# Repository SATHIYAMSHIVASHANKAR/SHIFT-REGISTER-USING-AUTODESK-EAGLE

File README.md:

# SHIFT-REGISTER-USING-AUTODESK-EAGLE
DEVELOPING SHIFT REGISTER USING IC 74595 IN AUTODESK EAGLE
***
step 1: In Autodesk Eagle, create a new project under the project sector. Name the file as Shift Register. Now under Shift Register create a Schematic file.
***
step 2: Allocate nessasary grid lines value in the grid section such that the editor page comes with the sutable grid lines
***
step 3: Using Add components tool, take the required parts and place it in the schematic with refernce to the circuit diagram. 
***
step 4: In order to reduce the complexcity in wire connection, introduce bus connection using Bus tool.
***
step 5: In Bus connection, it is mandatory to give Alias name and the Specification. Through this we can connet the Net (wire) conection at ease.
***
step 6: Now connect the components in the schematic using Net tool. 
***
step 7: Refer the data sheet to allocate the values to the components by using Value tool.
***
step 8 Its is mandatory to create a Net class for the ciruit made in Schematic. Create a net class, name it as Power and add the nessasary values to the Member section. Enter the respective terms to Default and Power sections.
***
step 9: To frame the entire circuit, select a Frame of your choice in Add components tool, place it around the circuit in schematic.
***
step 10: Now create a board, such that the diamentions of the board must be 80*60 mm
***
step 11: Move the components into the board and route the components using Air Routeing tool.
***
step 12: Select Polygon tool and extend its strech to the entire board. Name it as Ground. Now by appling Ratsnest tool, the polygon (ground) gets activated.
***
step 13: To give the name to board use Name tool. Enter the appropriate name and place it on the board with the Name Layer activated.
***
step 14: Drill four holes in each corner using Hole tool. By accessing Manufacturing tool we will get to know about the completed PCB board.
***

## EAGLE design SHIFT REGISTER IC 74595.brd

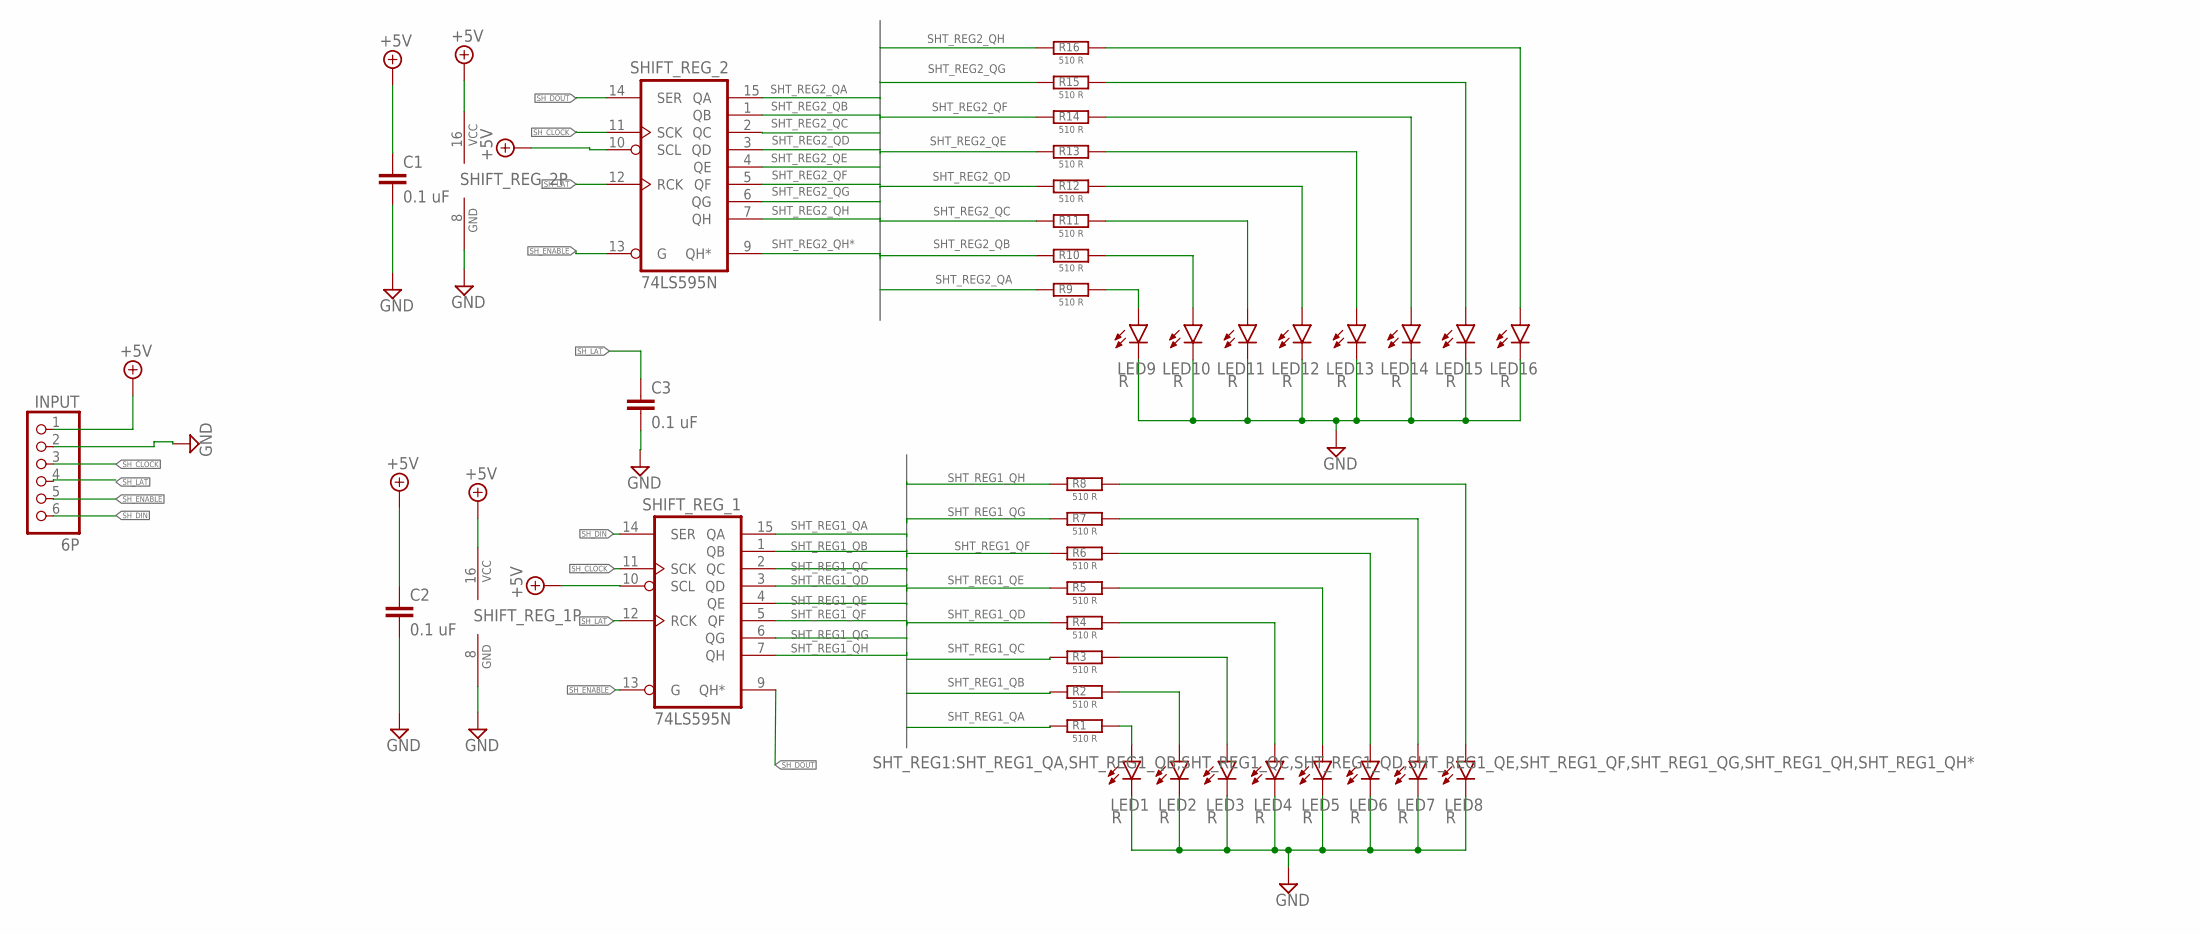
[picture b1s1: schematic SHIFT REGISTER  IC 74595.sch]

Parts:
C1, C2, C3: 0.1 uF; C050-030X075
INPUT: 6P; 1X06/90
LED1, LED2, LED3, LED4, LED5, LED6, LED7, LED8, LED9, LED10, LED11, LED12, LED13, LED14, LED15, LED16: R; LED5MM
R1, R2, R3, R4, R5, R6, R7, R8, R9, R10, R11, R12, R13, R14, R15, R16: 510 R; 0207/10
SHIFT_REG_1, SHIFT_REG_2: 74LS595N; DIL16

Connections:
+5V: C1.1, C2.1, INPUT.1, SHIFT_REG_1.10 (SCL), SHIFT_REG_1.16 (VCC), SHIFT_REG_2.10 (SCL), SHIFT_REG_2.16 (VCC)
GND: C1.2, C2.2, C3.2, INPUT.2, LED1.K (C), LED2.K (C), LED3.K (C), LED4.K (C), LED5.K (C), LED6.K (C), LED7.K (C), LED8.K (C), LED9.K (C), LED10.K (C), LED11.K (C), LED12.K (C), LED13.K (C), LED14.K (C), LED15.K (C), LED16.K (C), SHIFT_REG_1.8 (GND), SHIFT_REG_2.8 (GND)
unnamed: LED1.A, R1.2
unnamed: LED2.A, R2.2
unnamed: LED3.A, R3.2
unnamed: LED4.A, R4.2
unnamed: LED5.A, R5.2
unnamed: LED6.A, R6.2
unnamed: LED7.A, R7.2
unnamed: LED8.A, R8.2
unnamed: LED9.A, R9.2
unnamed: LED10.A, R10.2
unnamed: LED11.A, R11.2
unnamed: LED12.A, R12.2
unnamed: LED13.A, R13.2
unnamed: LED14.A, R14.2
unnamed: LED15.A, R15.2
unnamed: LED16.A, R16.2
SHT_REG1_QA: R1.1, SHIFT_REG_1.15 (QA)
SHT_REG1_QB: R2.1, SHIFT_REG_1.1 (QB)
SHT_REG1_QC: R3.1, SHIFT_REG_1.2 (QC)
SHT_REG1_QD: R4.1, SHIFT_REG_1.3 (QD)
SHT_REG1_QE: R5.1, SHIFT_REG_1.4 (QE)
SHT_REG1_QF: R6.1, SHIFT_REG_1.5 (QF)
SHT_REG1_QG: R7.1, SHIFT_REG_1.6 (QG)
SHT_REG1_QH: R8.1, SHIFT_REG_1.7 (QH)
SHT_REG2_QA: R9.1, SHIFT_REG_2.15 (QA)
SHT_REG2_QB: R10.1, SHIFT_REG_2.1 (QB)
SHT_REG2_QC: R11.1, SHIFT_REG_2.2 (QC)
SHT_REG2_QD: R12.1, SHIFT_REG_2.3 (QD)
SHT_REG2_QE: R13.1, SHIFT_REG_2.4 (QE)
SHT_REG2_QF: R14.1, SHIFT_REG_2.5 (QF)
SHT_REG2_QG: R15.1, SHIFT_REG_2.6 (QG)
SHT_REG2_QH: R16.1, SHIFT_REG_2.7 (QH)
SHT_REG2_QH*: SHIFT_REG_2.9 (QH*)
SH_CLOCK: INPUT.3, SHIFT_REG_1.11 (SCK), SHIFT_REG_2.11 (SCK)
SH_DIN: INPUT.6, SHIFT_REG_1.14 (SER)
SH_DOUT: SHIFT_REG_1.9 (QH*), SHIFT_REG_2.14 (SER)
SH_ENABLE: INPUT.5, SHIFT_REG_1.13 (G), SHIFT_REG_2.13 (G)
SH_LAT: C3.1, INPUT.4, SHIFT_REG_1.12 (RCK), SHIFT_REG_2.12 (RCK)

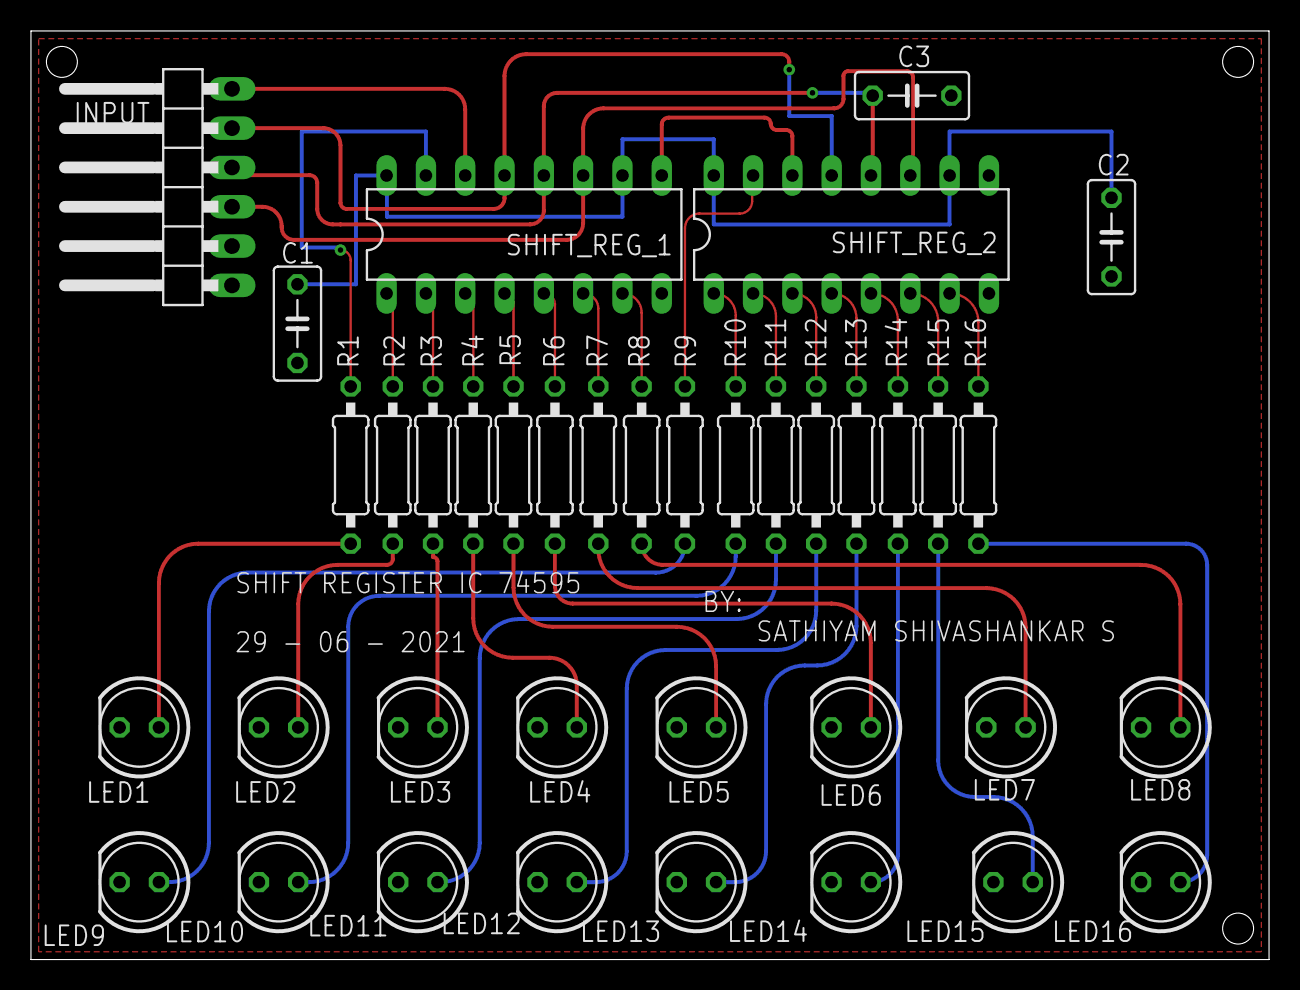
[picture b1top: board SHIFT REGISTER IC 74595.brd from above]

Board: 2 copper layers, 80.0 x 60.0 mm, 38 parts (0 on the bottom side), 39 nets.
